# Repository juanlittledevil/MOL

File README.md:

# MOL

Dual ADSR/VCA combo module for Eurorack.

For more details check my blog post here: www.scruffycatstudios.com/posts/degvca/
part 2 here: www.scruffycatstudios.com/posts/degvca-part2/
And YouTube here: https://www.youtube.com/watch?v=CZ0J_sP1nE4&list=PLdO1IhDAhMdK4l8dJ0V3lOzin-maOEFXo

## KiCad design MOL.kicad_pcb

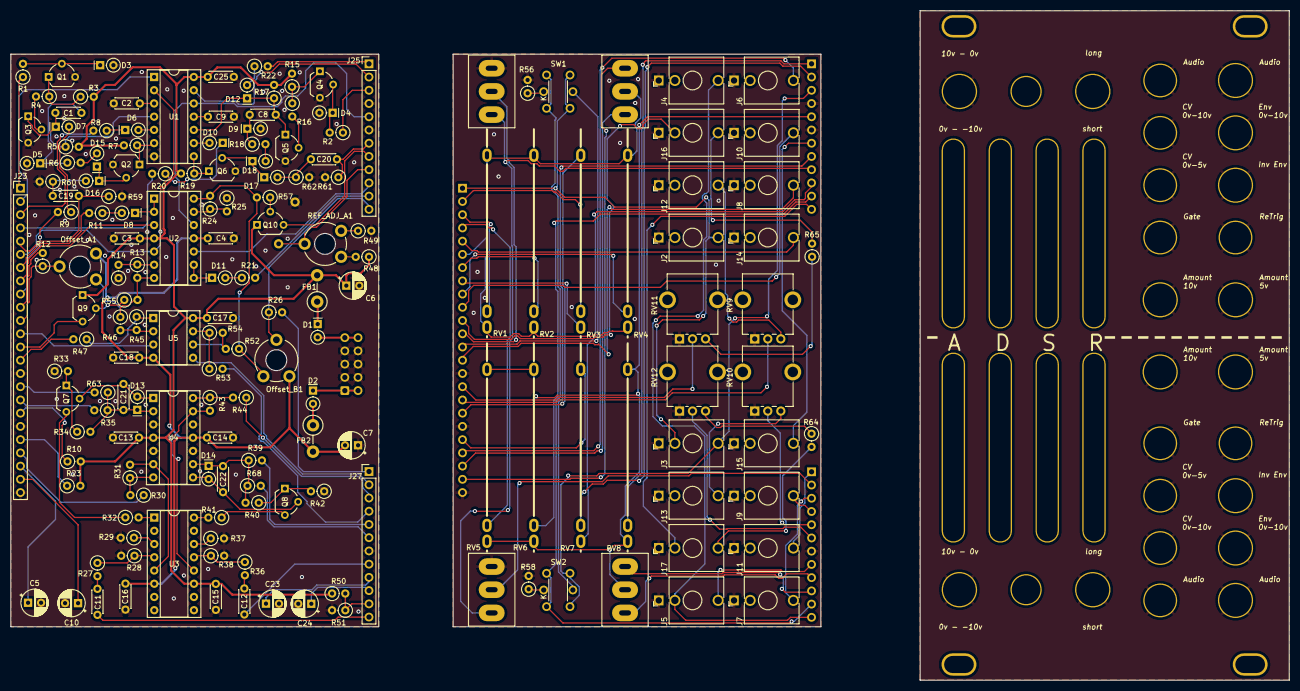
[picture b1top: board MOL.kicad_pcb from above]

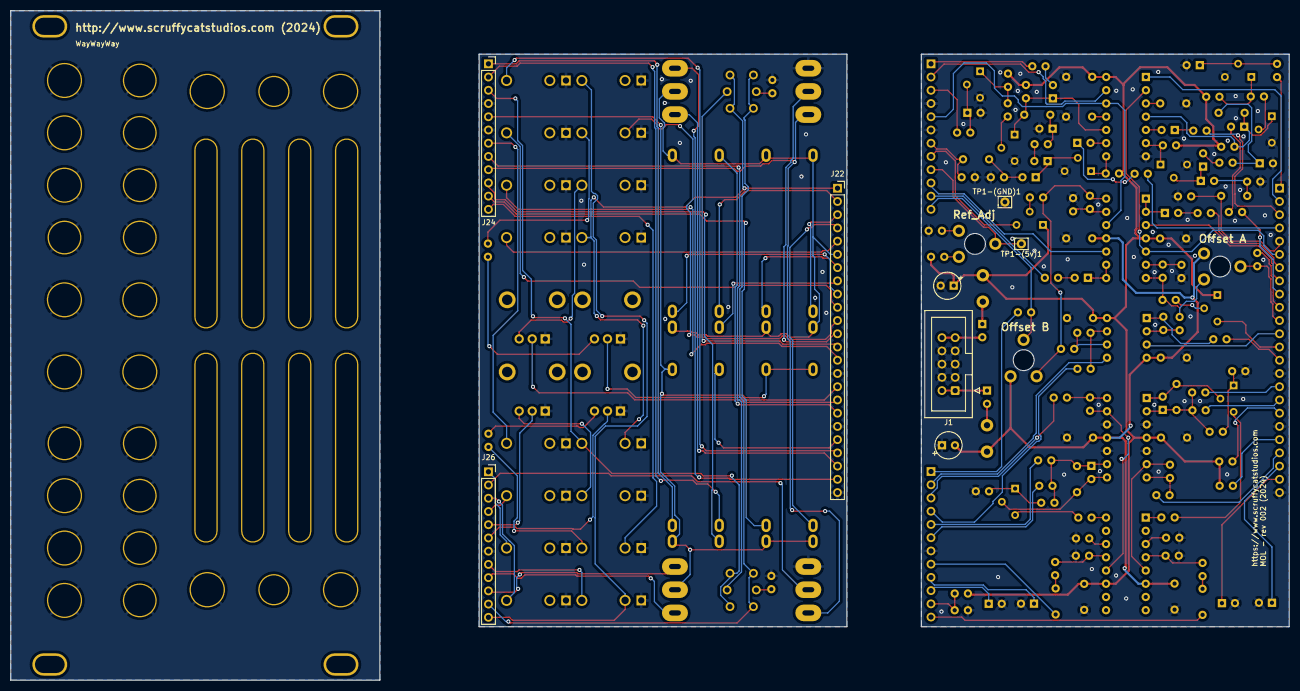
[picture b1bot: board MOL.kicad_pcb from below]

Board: 2 copper layers, 245.4 x 128.5 mm, 210 parts (6 on the bottom side), 161 nets.

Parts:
BH1, BH2: LED Button; LED-ButtonHole
C1, C2, C8, C9, C19, C20: 10n; C_Disc_D4.3mm_W1.9mm_P5.00mm
C3, C4, C11, C12, C13, C14, C15, C16, C17, C18, C25: 100n; C_Disc_D4.3mm_W1.9mm_P5.00mm
C5, C23: 47uF; CP_Radial_D5.0mm_P2.50mm
C6, C7: 10uF; CP_Radial_D5.0mm_P2.50mm
C10, C24: 4.7uF; CP_Radial_D5.0mm_P2.50mm
C21, C22: 1n; C_Disc_D4.3mm_W1.9mm_P5.00mm
D1, D2: Schottky; D_DO-35_SOD27_P2.54mm_Vertical_KathodeUp
D3, D4, D5, D6, D7, D8, D9, D10, D11, D12, D13, D14, D15, D16, D17, D18: 1N4148; D_DO-35_SOD27_P2.54mm_Vertical_KathodeUp
FB1, FB2: FerriteBead; R_Axial_DIN0411_L9.9mm_D3.6mm_P5.08mm_Vertical
J1: EuroRack Power; IDC-Header_2x05_P2.54mm_Vertical
J2: Gate In A; Jack_3.5mm_QingPu_thonk-PJ398SM_Vertical_CircularHoles
J3: Gate In B; Jack_3.5mm_QingPu_thonk-PJ398SM_Vertical_CircularHoles
J4: Audio In A_(C); Jack_3.5mm_QingPu_thonk-PJ398SM_Vertical_CircularHoles
J5: Audio In B_(C); Jack_3.5mm_QingPu_thonk-PJ398SM_Vertical_CircularHoles
J6: Audio Out A_(C); Jack_3.5mm_QingPu_thonk-PJ398SM_Vertical_CircularHoles
J7: Audio Out B_(C); Jack_3.5mm_QingPu_thonk-PJ398SM_Vertical_CircularHoles
J8: Inv CV Out A (10v - 0v); Jack_3.5mm_QingPu_thonk-PJ398SM_Vertical_CircularHoles
J9: Inv CV Out B (10v - 0v); Jack_3.5mm_QingPu_thonk-PJ398SM_Vertical_CircularHoles
J10: CV Out A (0v - 10v); Jack_3.5mm_QingPu_thonk-PJ398SM_Vertical_CircularHoles
J11: CV Out B (0v - 10v); Jack_3.5mm_QingPu_thonk-PJ398SM_Vertical_CircularHoles
J12: CV In A (0v - 5v); Jack_3.5mm_QingPu_thonk-PJ398SM_Vertical_CircularHoles
J13: CV In B (0v - 5v); Jack_3.5mm_QingPu_thonk-PJ398SM_Vertical_CircularHoles
J14: Re-Trigger A_(C); Jack_3.5mm_QingPu_thonk-PJ398SM_Vertical_CircularHoles
J15: Re-Trigger B_(C); Jack_3.5mm_QingPu_thonk-PJ398SM_Vertical_CircularHoles
J16: CV In A (0v - 10v); Jack_3.5mm_QingPu_thonk-PJ398SM_Vertical_CircularHoles
J17: CV In B (0v - 10v); Jack_3.5mm_QingPu_thonk-PJ398SM_Vertical_CircularHoles
J18, J19, J20, J21: Screw Hole; ScrewHole_Oval
J22: Conn_01x24_Socket; PinSocket_1x24_P2.54mm_Vertical
J23: Conn_01x24_Pin; PinHeader_1x24_P2.54mm_Vertical
J24, J26: Conn_01x12_Socket; PinSocket_1x12_P2.54mm_Vertical
J25, J27: Conn_01x12_Pin; PinHeader_1x12_P2.54mm_Vertical
JH1, JH2, JH3, JH4, JH7, JH9, JH10, JH11, JH12, JH14: 3.5mm Jack; JackHole_3.5mm
JH5, JH6, JH8, JH13, JH15, JH16: 3.5mm Jack; JackHole_3.5mm-OUT
Offset_A1: 5k; Potentiometer_Trim_Vertical_THL
Offset_B1: 5k; Potentiometer_Trim_Vertical_THL
PH1, PH2, PH3, PH4, PH5, PH6, PH7, PH8: 30mm Vertical Slider; PotHole_Slide_open_oval
PH9, PH10, PH11, PH12: Pot Jack (no-mount); PotHole_no-mount
Q1, Q2, Q3, Q4, Q5, Q6, Q9, Q10: BC547; TO-92_Wide
Q7, Q8: 2N3906; TO-92_Wide
R1, R2, R6, R18, R55, R57: 10k; R_Axial_DIN0207_L6.3mm_D2.5mm_P2.54mm_Vertical
R3, R5, R7, R15, R17, R19: 4.7k; R_Axial_DIN0207_L6.3mm_D2.5mm_P2.54mm_Vertical
R4, R16: 22k; R_Axial_DIN0207_L6.3mm_D2.5mm_P2.54mm_Vertical
R8, R9, R11, R20, R21, R22: 22; R_Axial_DIN0207_L6.3mm_D2.5mm_P2.54mm_Vertical
R10, R23, R49: 27k; R_Axial_DIN0207_L6.3mm_D2.5mm_P2.54mm_Vertical
R12, R26, R30, R33, R42, R44, R47, R53: 1k; R_Axial_DIN0207_L6.3mm_D2.5mm_P2.54mm_Vertical
R13, R24, R31, R43, R48: 39k; R_Axial_DIN0207_L6.3mm_D2.5mm_P2.54mm_Vertical
R14, R25: 150k; R_Axial_DIN0207_L6.3mm_D2.5mm_P2.54mm_Vertical
R27, R36, R45, R46, R52, R54, R59, R60, R61, R62, R64, R65: 100k; R_Axial_DIN0207_L6.3mm_D2.5mm_P2.54mm_Vertical
R28, R29, R37, R38: 330; R_Axial_DIN0207_L6.3mm_D2.5mm_P2.54mm_Vertical
R32, R41: 6.8k; R_Axial_DIN0207_L6.3mm_D2.5mm_P2.54mm_Vertical
R34, R40: 33k; R_Axial_DIN0207_L6.3mm_D2.5mm_P2.54mm_Vertical
R35, R39, R51, R63, R68: 330k; R_Axial_DIN0207_L6.3mm_D2.5mm_P2.54mm_Vertical
R50: 470k; R_Axial_DIN0207_L6.3mm_D2.5mm_P2.54mm_Vertical
R56, R58: 2.2k; R_Axial_DIN0207_L6.3mm_D2.5mm_P2.54mm_Vertical
REF_ADJ_A1: 5k; Potentiometer_Trim_Vertical_THL
RV1: Attack A; Potentiometer_Slide_open_THL
RV2: Decay A; Potentiometer_Slide_open_THL
RV3: Sustain A; Potentiometer_Slide_open_THL
RV4: Release A; Potentiometer_Slide_open_THL
RV5: Attack B; Potentiometer_Slide_open_THL
RV6: Decay B; Potentiometer_Slide_open_THL
RV7: Sustain B; Potentiometer_Slide_open_THL
RV8: Release B; Potentiometer_Slide_open_THL
RV9, RV10, RV11, RV12: 100k; Potentiometer_Alpha_RD901F-40-00D_Single_Vertical_CircularH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
SH1, SH2, SH3, SH4: Switch Jack; SwitchHole_screw-mount
SW1, SW2: SW_Push_LED; SW_PushButton_LED_E-Type-A
SW3: Inv Offset A; SW_Toggle_Blue_wSlots
SW4: Inv Offset B; SW_Toggle_Blue_wSlots
SW5: Length A; SW_Toggle_Blue_wSlots
SW6: Length B; SW_Toggle_Blue_wSlots
TP1-(5v)1, TP1-(GND)1: TestPoint; Pin_D0.9mm_L10.0mm_W2.4mm_FlatFork
U1: LM556; DIP-14_W7.62mm_Socket
U2, U4: TL074; DIP-14_W7.62mm_Socket
U3: LM13700; DIP-16_W7.62mm_Socket
U5: TL072; DIP-8_W7.62mm_Socket

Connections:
+12V: C3.1, C6.1, C13.1, C15.1, C17.1, C25.1, FB1.2, Q9.1 (C), Q10.1 (C), R3.2, R5.2, R7.2, R10.2, R15.2, R17.2, R19.2, R23.2, R48.1, R50.1, U1.14 (VCC), U2.4 (V+), U3.11 (V+), U4.4 (V+), U5.8 (V+)
-12V: C4.2, C7.2, C14.2, C16.2, C18.2, FB2.2, Offset_A1.1, Offset_B1.1, U2.11 (V-), U3.6 (V-), U4.11 (V-), U5.4 (V-)
/Control/5.4v_(C): J26.11, SW1.1, SW2.1
/Control/5v_ref: J25.9, REF_ADJ_A1.2, TP1-(5v)1.1
/Control/5v_ref_(C): J24.9, SW3.1 (A), SW4.1 (A)
/Control/Attack_1_A: J23.3, R8.2
/Control/Attack_1_A_(C): J22.3, RV1.1
/Control/Attack_1_B: J23.4, R20.2
/Control/Attack_1_B_(C): J22.4, RV5.1
/Control/Audio_In_A: C11.1, J27.12
/Control/Audio_In_A_(C): J4.2, J5.3, J26.12
/Control/Audio_In_B: C12.1, J27.8
/Control/Audio_In_B_(C): J5.2, J26.8
/Control/Audio_Out_A: J23.21, R30.1
/Control/Audio_Out_A_(C): J6.2, J22.21
/Control/Audio_Out_B: J27.3, R44.1
/Control/Audio_Out_B_(C): J7.2, J26.3
/Control/CV_In_5v_A: J23.17, R35.2
/Control/CV_In_5v_A_(C): J22.17, RV9.2
/Control/CV_In_5v_B: J27.5, R39.2
/Control/CV_In_5v_B_(C): J26.5, RV10.2
/Control/CV_In_10v_A: J23.16, R63.2
/Control/CV_In_10v_A_(C): J22.16, RV11.2
/Control/CV_In_10v_B: J27.6, R68.2
/Control/CV_In_10v_B_(C): J26.6, RV12.2
/Control/Decay_1_A: J23.7, R11.2
/Control/Decay_1_A_(C): J22.7, RV2.1
/Control/Decay_1_B: J25.11, R21.2
/Control/Decay_1_B_(C): J24.11, RV6.1
/Control/Discharge_A: J23.6, U1.2 (THR), U2.5 (+)
/Control/Discharge_A_(C): J22.6, RV1.2, RV1.3, RV2.2, RV2.3, RV4.2, RV4.3, SW5.2 (B)
/Control/Discharge_B: J25.5, U1.12 (THR), U2.12 (+)
/Control/Discharge_B_(C): J24.5, RV5.2, RV5.3, RV6.2, RV6.3, RV8.2, RV8.3, SW6.2 (B)
/Control/EG_LED_Anode_A: J23.13, Q9.3 (E)
/Control/EG_LED_Anode_A_(C): J22.13, SW1.4 (A)
/Control/EG_LED_Anode_B: J25.8, Q10.3 (E)
/Control/EG_LED_Anode_B_(C): J24.8, SW2.4 (A)
/Control/Env_A: J23.11, Offset_A1.2, R12.1
/Control/Env_A_(C): J16.3, J22.11
/Control/Env_B: J25.12, Offset_B1.2, R26.1
/Control/Env_B_(C): J17.3, J24.12
/Control/Env_Out_A: J23.10, R12.2
/Control/Env_Out_A_(C): J10.2, J22.10
/Control/Env_Out_B: J27.1, R26.2
/Control/Env_Out_B_(C): J11.2, J26.1
/Control/Gate_in_A: J23.1, R1.1
/Control/Gate_in_A_(C): J2.2, J3.3, J22.1, SW1.2
/Control/Gate_in_B: J25.3, R2.1
/Control/Gate_in_B_(C): J3.2, J24.3, SW2.2
/Control/InvEnv_Out_A: J23.14, R47.2
/Control/InvEnv_Out_A_(C): J8.2, J22.14
/Control/InvEnv_Out_B: J27.4, R53.2
/Control/InvEnv_Out_B_(C): J9.2, J26.4
/Control/Long_A: C5.1, J23.22
/Control/Long_A_(C): J22.22, SW5.1 (A)
/Control/Long_B: C23.1, J27.9
/Control/Long_B_(C): J26.9, SW6.1 (A)
/Control/ReTrigger_A: C19.1, J23.5, R59.1
/Control/ReTrigger_A_(C): J14.2, J22.5
/Control/ReTrigger_B: C20.1, J25.7, R61.1
/Control/ReTrigger_B_(C): J15.2, J24.7
/Control/Release_1_A: J23.9, R9.2
/Control/Release_1_A_(C): J22.9, RV4.1
/Control/Release_1_B: J25.1, R22.2
/Control/Release_1_B_(C): J24.1, RV8.1
/Control/Short_A: C10.1, J23.23
/Control/Short_A_(C): J22.23, SW5.3 (C)
/Control/Short_B: C24.1, J27.10
/Control/Short_B_(C): J26.10, SW6.3 (C)
/Control/Sustain_1_A: J23.2, U1.1 (DIS)
/Control/Sustain_1_A_(C): J22.2, RV3.1
/Control/Sustain_1_B: J25.2, U1.13 (DIS)
/Control/Sustain_1_B_(C): J24.2, RV7.1
/Control/Sustain_2_A: J23.8, U2.3 (+)
/Control/Sustain_2_A_(C): J22.8, RV3.2
/Control/Sustain_2_B: J25.10, U2.10 (+)
/Control/Sustain_2_B_(C): J24.10, RV7.2
/Control/Sustain_3_A: J23.18, R10.1
/Control/Sustain_3_A_(C): J22.18, RV3.3
/Control/Sustain_3_B: J23.20, R23.1
/Control/Sustain_3_B_(C): J22.20, RV7.3
/Control/inv_offset_A: J23.12, U5.3 (+)
/Control/inv_offset_A_(C): J22.12, SW3.2 (B)
/Control/inv_offset_B: J27.2, U5.5 (+)
/Control/inv_offset_B_(C): J26.2, SW4.2 (B)
/Fastest ADSR in the West/5.4v_Ref: J27.11, R50.2, R51.1
/Fastest ADSR in the West/Reset_A: C1.1, D7.1 (K), Q3.1 (C), R5.1, U1.4 (R)
/Fastest ADSR in the West/Reset_B: C8.1, D12.1 (K), Q5.1 (C), R17.1, U1.10 (R)
/Power Supply/EuroPower-neg: D2.1 (K), J1.1, J1.2
/Power Supply/EuroPower-pos: D1.2 (A), J1.9, J1.10
/Power Supply/PolNeg: D2.2 (A), FB2.1
/Power Supply/PolPlus: D1.1 (K), FB1.1
GND: C2.2, C3.2, C4.1, C5.2, C6.2, C7.1, C9.2, C10.2, C13.2, C14.1, C15.2, C16.1, C17.2, C18.1, C23.2, C24.2, C25.2, D3.2 (A), D4.2 (A), D5.2 (A), D9.2 (A), J1.3, J1.4, J1.5, J1.6, J1.7, J1.8, J2.1, J3.1, J4.1, J5.1, J6.1, J7.1, J8.1, J9.1, J10.1, J11.1, J12.1, J13.1, J14.1, J15.1, J16.1, J17.1, J22.15, J22.19, J22.24, J23.15, J23.19, J23.24, J24.4, J24.6, J25.4, J25.6, J26.7, J27.7, JH1.1, JH2.1, JH3.1, JH4.1, JH5.1, JH6.1, JH7.1, JH8.1, JH9.1, JH10.1, JH11.1, JH12.1, JH13.1, JH14.1, JH15.1, JH16.1, PH9.1, PH10.1, PH11.1, PH12.1, Q1.3 (E), Q2.3 (E), Q3.3 (E), Q4.3 (E), Q5.3 (E), Q6.3 (E), R14.1, R25.1, R28.2, R29.2, R33.1, R37.2, R38.2, R42.1, R49.2, R51.2, R56.2, R58.2, R59.2, R60.2, R61.2, R62.2, RV9.1, RV10.1, RV11.1, RV12.1, SH1.1, SH2.1, SH3.1, SH4.1, SW3.3 (C), SW4.3 (C), TP1-(GND)1.1, U1.7 (GND), U4.3 (+), U4.5 (+), U4.10 (+), U4.12 (+)
unnamed: C11.2, R27.2
unnamed: C12.2, R36.2
unnamed: D3.1 (K), Q1.2 (B), R1.2
unnamed: D4.1 (K), Q4.2 (B), R2.2
unnamed: C1.2, D5.1 (K), R6.1
unnamed: D6.2 (A), U1.5 (Q)
unnamed: D6.1 (K), R8.1
unnamed: D7.2 (A), R9.1
unnamed: D8.2 (A), R11.1
unnamed: D8.1 (K), U2.1, U2.2 (-)
unnamed: C8.2, D9.1 (K), R18.1
unnamed: D10.2 (A), U1.9 (Q)
unnamed: D10.1 (K), R20.1
unnamed: D11.2 (A), R21.1
unnamed: D11.1 (K), U2.8, U2.9 (-)
unnamed: D12.2 (A), R22.1
unnamed: C21.2, D13.2 (A), Q7.2 (B), U4.1
unnamed: C21.1, D13.1 (K), R34.2, R35.1, R63.1, U4.2 (-)
unnamed: C22.2, D14.2 (A), Q8.2 (B), U4.8
unnamed: C22.1, D14.1 (K), R39.1, R40.2, R68.1, U4.9 (-)
unnamed: D15.2 (A), R6.2
unnamed: D15.1 (K), D16.1 (K), Q2.2 (B)
unnamed: C19.2, D16.2 (A), R60.1
unnamed: C20.2, D17.2 (A), R62.1
unnamed: D17.1 (K), D18.1 (K), Q6.2 (B)
unnamed: D18.2 (A), R18.2
unnamed: J12.2, RV9.3
unnamed: J13.2, RV10.3
unnamed: J16.2, R65.2
unnamed: J17.2, R64.2
unnamed: Offset_A1.3, R13.2, R46.1, R55.2, U2.7
unnamed: Offset_B1.3, R24.2, R52.1, R57.2, U2.14
unnamed: Q1.1 (C), R3.1, R4.1
unnamed: Q2.1 (C), R7.1, U1.6 (TR)
unnamed: Q3.2 (B), R4.2
unnamed: Q4.1 (C), R15.1, R16.1
unnamed: Q5.2 (B), R16.2
unnamed: Q6.1 (C), R19.1, U1.8 (TR)
unnamed: Q7.3 (C), R32.1
unnamed: Q7.1 (E), R33.2, R34.1
unnamed: Q8.3 (C), R41.1
unnamed: Q8.1 (E), R40.1, R42.2
unnamed: Q9.2 (B), R55.1
unnamed: Q10.2 (B), R57.1
unnamed: R30.2, R31.1, U4.7
unnamed: R32.2, U3.1
unnamed: R41.2, U3.16
unnamed: R43.1, R44.2, U4.14
unnamed: R45.1, R47.1, U5.1
unnamed: R48.2, REF_ADJ_A1.3
unnamed: R49.1, REF_ADJ_A1.1
unnamed: R53.1, R54.1, U5.7
unnamed: R64.1, RV12.3
unnamed: R65.1, RV11.3
unnamed: R56.1, SW1.3 (K)
unnamed: R58.1, SW2.3 (K)
unnamed: C2.1, U1.3 (CV)
unnamed: C9.1, U1.11 (CV)
unnamed: R13.1, R14.2, U2.6 (-)
unnamed: R24.1, R25.2, U2.13 (-)
unnamed: R37.1, U3.14 (+)
unnamed: R36.1, R38.1, U3.13 (-)
unnamed: R29.1, U3.3 (+)
unnamed: R27.1, R28.1, U3.4 (-)
unnamed: R31.2, U3.5, U4.6 (-)
unnamed: R43.2, U3.12, U4.13 (-)
unnamed: R45.2, R46.2, U5.2 (-)
unnamed: R52.2, R54.2, U5.6 (-)

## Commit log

2024-01-25 part 2
2024-01-25 images
